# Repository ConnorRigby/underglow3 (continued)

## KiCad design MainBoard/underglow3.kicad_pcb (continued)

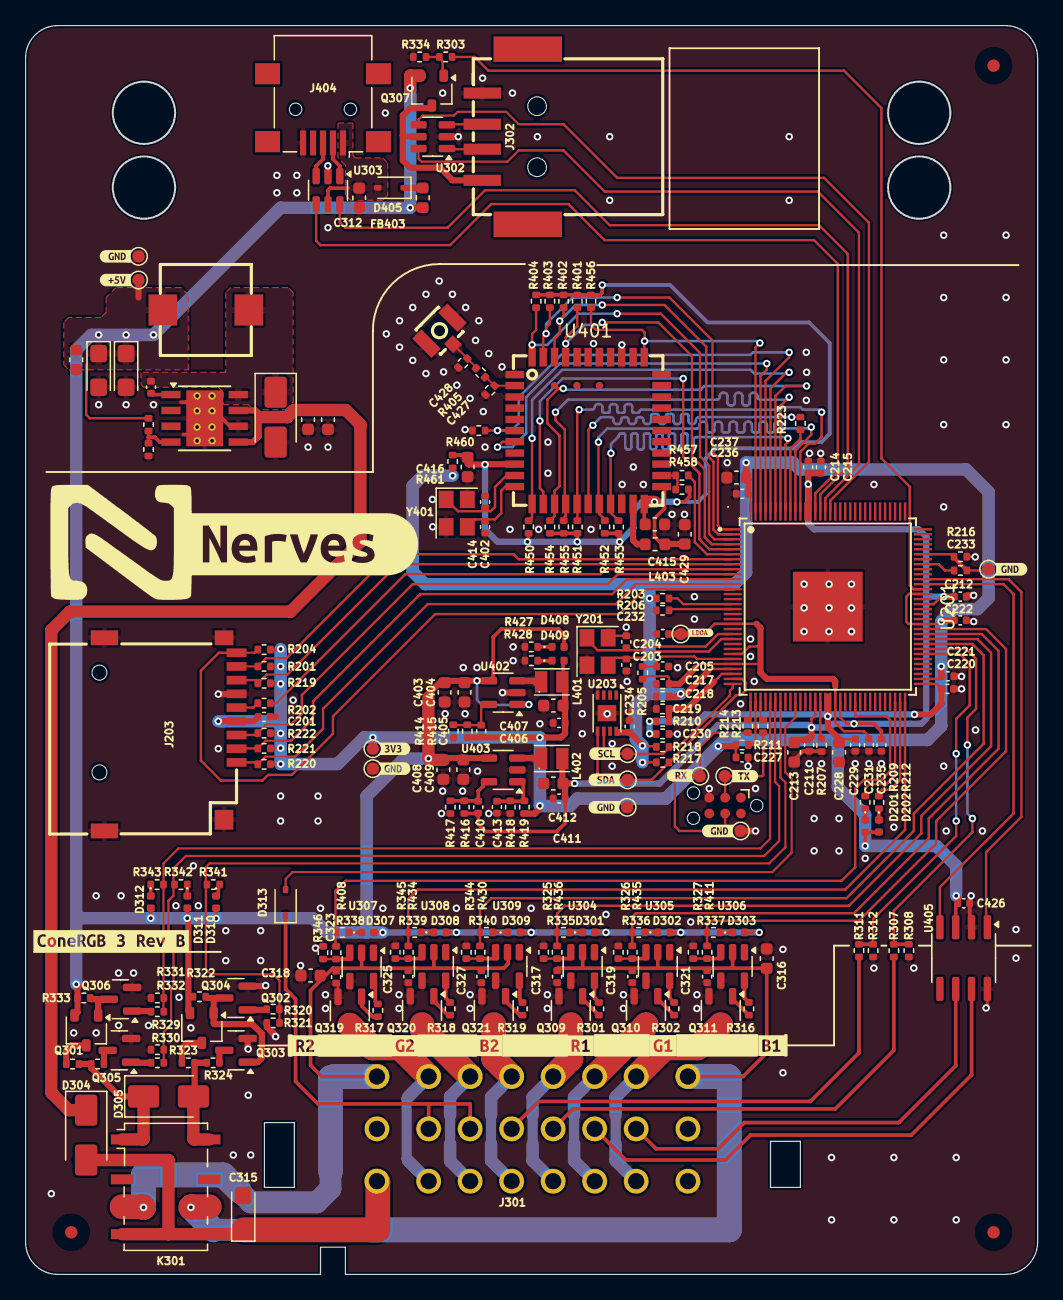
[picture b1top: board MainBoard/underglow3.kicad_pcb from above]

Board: 4 copper layers, 81.2 x 100.2 mm, 246 parts (0 on the bottom side), 145 nets.

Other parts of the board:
Enclosure: TestPoint_Pad_D1.0mm
TP: GND; TestPoint_Pad_D1.0mm
TP#2: GND; TestPoint_Pad_D1.0mm
U201: T113-S3; LQFP-128_L14.0-W14.0-P0.40-LS16.0-BL-EP5.6
kibuzzard-65F09AC9: G***; kibuzzard-65F09AC9
kibuzzard-65F09B04: G***; kibuzzard-65F09B04
kibuzzard-65F09B16: G***; kibuzzard-65F09B16
kibuzzard-65F09B27: G***; kibuzzard-65F09B27
kibuzzard-65F09B40: G***; kibuzzard-65F09B40
kibuzzard-65F09B51: G***; kibuzzard-65F09B51
kibuzzard-65F09C6B: G***; kibuzzard-65F09C6B
kibuzzard-65F09CD2: G***; kibuzzard-65F09CD2
kibuzzard-65F09CF9: G***; kibuzzard-65F09CF9
kibuzzard-65F09D0C: G***; kibuzzard-65F09D0C
kibuzzard-65F09D1C, kibuzzard-65F09D1C#2: G***; kibuzzard-65F09D1C
kibuzzard-65FE52BD: G***; kibuzzard-65FE52BD
kibuzzard-65FE522B: G***; kibuzzard-65FE522B
kibuzzard-65FEF020: G***; kibuzzard-65FEF020
kibuzzard-65FEF408: G***; kibuzzard-65FEF408
kibuzzard-65FEF568: G***; kibuzzard-65FEF568
kibuzzard-666C6B51: G***; kibuzzard-666C6B51
kibuzzard-6669C582: G***; kibuzzard-6669C582
kibuzzard-6669C587: G***; kibuzzard-6669C587

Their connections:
+0v9: U201.46 (VDD-SYS0), U201.51 (VDD-SYS0), U201.81 (VDD-SYS2), U201.116 (VDD-CORE0), U201.117 (VDD-CORE1); also elsewhere on the board
+1V8A: U201.89 (AVCC); also elsewhere on the board
+3V3: U201.29 (LDO-IN), U201.66 (VCC-PD), U201.77 (VCC-TVOUT), U201.83 (VCC-IO), U201.128 (VCC-PG); also elsewhere on the board
/Application/AP_WAKE_BT: U201.125 (PG13); also elsewhere on the board
/Application/BT_EN: U201.127 (PG15); also elsewhere on the board
/Application/BT_WAKE_AP: U201.126 (PG14); also elsewhere on the board
/Application/CAN0_RX: U201.85 (PB3); also elsewhere on the board
/Application/CAN0_TX: U201.86 (PB2); also elsewhere on the board
/Application/DZQ: U201.47 (DZQ); also elsewhere on the board
/Application/HCI_CTS: U201.4 (PG9); also elsewhere on the board
/Application/HCI_RTS: U201.3 (PG8); also elsewhere on the board
/Application/HCI_RX: U201.2 (PG7); also elsewhere on the board
/Application/HCI_TX: U201.1 (PG6); also elsewhere on the board
/Application/I2C_SCL: U201.32 (PE12); also elsewhere on the board
/Application/I2C_SDA: U201.31 (PE13); also elsewhere on the board
/Application/LDOA_OUT: U201.20 (VCC-PLL), U201.26 (VCC-RTC), U201.28 (LDOA-OUT), U201.50 (VDD18-DRAM); also elsewhere on the board
/Application/LDOB_OUT: U201.30 (LDOB-OUT); also elsewhere on the board
/Application/LEDC: U201.42 (PE5); also elsewhere on the board
/Application/LED_ST1: U201.62 (PD7); also elsewhere on the board
/Application/LED_ST2: U201.63 (PD8); also elsewhere on the board
/Application/PWM0: U201.73 (PD16); also elsewhere on the board
/Application/PWM1: U201.74 (PD17); also elsewhere on the board
/Application/PWM2: U201.75 (PD18); also elsewhere on the board
/Application/PWM3: U201.76 (PD19); also elsewhere on the board
/Application/PWM4: U201.54 (PD20); also elsewhere on the board
/Application/PWM6: U201.64 (PD9); also elsewhere on the board
/Application/RELAY_COIL_GND: U201.38 (PE9); also elsewhere on the board
/Application/RELAY_COIL_VDC: U201.37 (PE10); also elsewhere on the board
/Application/RELAY_SW: U201.39 (PE8); also elsewhere on the board
/Application/RST: U201.27 (RST); also elsewhere on the board
/Application/SDCO0_CLK: U201.9 (PF2); also elsewhere on the board
/Application/SDCO0_CMD: U201.10 (PF3); also elsewhere on the board
/Application/SDCO0_D0: U201.8 (PF1); also elsewhere on the board
/Application/SDCO0_D1: U201.7 (PF0); also elsewhere on the board
/Application/SDCO0_D2: U201.12 (PF5); also elsewhere on the board
/Application/SDCO0_D3: U201.11 (PF4); also elsewhere on the board
/Application/SD_DET: U201.13 (PF6); also elsewhere on the board
/Application/SPI0_CLK: U201.19 (PC2); also elsewhere on the board
/Application/SPI0_CS0: U201.18 (PC3); also elsewhere on the board
/Application/SPI0_HLD: U201.14 (PC7); also elsewhere on the board
/Application/SPI0_MISO: U201.16 (PC5); also elsewhere on the board
/Application/SPI0_MOSI: U201.17 (PC4); also elsewhere on the board
/Application/SPI0_WP: U201.15 (PC6); also elsewhere on the board
/Application/SUS_CLK: U201.6 (PG11); also elsewhere on the board
/Application/UART0_RX: U201.33 (PE3); also elsewhere on the board
/Application/UART0_TX: U201.35 (PE2); also elsewhere on the board
/Application/USB_SW: U201.84 (PB4); also elsewhere on the board
/Application/VCC_DRAM: U201.48 (VCC-DRAM0), U201.49 (VCC-DRAM1), U201.65 (VCC-LVDS); also elsewhere on the board
/Application/VCC_PE: U201.34 (VCC-PE); also elsewhere on the board
/Application/WIFI_CMD: U201.118 (PG1); also elsewhere on the board
/Application/WIFI_DAT0: U201.119 (PG2); also elsewhere on the board
/Application/WIFI_DAT1: U201.121 (PG3); also elsewhere on the board
/Application/WIFI_DAT2: U201.123 (PG4); also elsewhere on the board
/Application/WIFI_DAT3: U201.122 (PG5); also elsewhere on the board
/Application/WL_REG_ON: U201.124 (PG12); also elsewhere on the board
/Application/WL_WAKE_AP: U201.5 (PG10); also elsewhere on the board
/Application/XI: U201.23 (DXIN); also elsewhere on the board
/Application/XO: U201.22 (DXOUT); also elsewhere on the board
/Power/PI1_DIV: U201.72 (PD15); also elsewhere on the board
/Power/PI2_DIV: U201.71 (PD14); also elsewhere on the board
/Power/USB0_DN: U201.114 (USB0-DM); also elsewhere on the board
/Power/USB0_DP: U201.115 (USB0-DP); also elsewhere on the board
/Power/USB1_DN: U201.113 (USB1-DM); also elsewhere on the board
/Power/USB1_DP: U201.112 (USB1-DP); also elsewhere on the board
GND: TP.1, TP#2.1, U201.129 (EP); also elsewhere on the board
GNDA: U201.91 (AGND); also elsewhere on the board
unnamed 130: U201.120 (PG0); also elsewhere on the board

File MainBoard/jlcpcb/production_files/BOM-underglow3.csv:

Comment,Designator,Footprint,LCSC
450mΩ ±25% 600Ω@100MHz,FB403,L_0603_1608Metric,C1002
1k,"R209,R212,R301,R302,R303,R316,R317,R318,R319,R320,R330,R332,R335,R336,R337,R338,R339,R340,R341,R342,R343,R408,R411,R427,R428,R430,R434,R435,R436",R_0402_1005Metric,C11702
SN65HVD230,U405,SOIC-8_3.9x4.9mm_P1.27mm,C12084
2.2uF,"C217,C218,C219,C233",R_0402_1005Metric,C12530
SS210,"D304,D305,D306",D_SMA,C14996
22pF,"C203,C204,C405,C410",C_0402_1005Metric,C1555
0R,"R210,R211,R213,R214,R216,R405,R457,R460,R461",R_0402_1005Metric,C17168
NSR0320MW2T1G,"D313,D405",D_SOD-323,C191023
10uF,"C316,C318,C403,C404,C407,C408,C409,C412",C_0603_1608Metric,C19702
SI2302-TP,"Q309,Q310,Q311,Q319,Q320,Q321",SOT-23-3,C20917
24Mhz,Y201,Crystal_SMD_3225-4Pin_3.2x2.5mm,C2149059
G6K-2F-Y-TR DC3,K301,Relay_DPDT_Omron_G6K-2F-Y,C2153097
22R,"R202,R223,R306,R323,R324,R328",R_0402_1005Metric,C25092
240R,R207,R_0402_1005Metric,C25094
100k,"R201,R203,R204,R205,R206,R219,R220,R221,R222,R321,R322,R325,R326,R327,R329,R331,R333,R334,R344,R345,R346,R419,R450,R456",R_0402_1005Metric,C25741
10k,"R307,R311,R347",R_0402_1005Metric,C25744
150k,"R415,R417,R418",R_0402_1005Metric,C25755
47k,"R451,R452,R453,R454,R455,R458",R_0402_1005Metric,C25792
75k,R416,R_0402_1005Metric,C25798
2.2k,"R217,R218",R_0402_1005Metric,C25879
3.3k,R348,R_0402_1005Metric,C25890
4.7uH,L303,IND-SMD_L7.3-W7.3,C2826710
100nf,"C201,C205,C211,C212,C214,C215,C220,C221,C222,C227,C229,C231,C232,C234,C235,C236,C304,C317,C319,C321,C323,C325,C327,C406,C411,C413,C426",C_0402_1005Metric,C307331
LED,"D201,D202,D301,D302,D303,D307,D308,D309,D310,D311,D312,D408,D409",LED_0402_1005Metric,C364556
Micro_SD_Card_Det1,J203,TF-SMD_TF-PUSH,C393941
680k,R414,R_0402_1005Metric,C4131
SY8088IAAC,"U402,U403",SOT-23-5,C479072
BWU.FL-IPEX1,ANT401,IPEX-SMD_BWIPX-1-001E,C5137195
3.9k,"R308,R312",R_0402_1005Metric,C51721
T113-S3,U201,LQFP-128_L14.0-W14.0-P0.40-LS16.0-BL-EP5.6,C5197687
1uF,C230,R_0402_1005Metric,C52923
ATECC608A-MAHDA,U203,DFN-8-1EP_3x2mm_P0.5mm_EP1.3x1.5mm,C616908
10uF 16V,"C313,C314,C315",CP_EIA-3216-18_Kemet-A,C7171
USB_A,J302,USB-A-SMD_USB-234-BCW,C720528
USB_B_Mini,J404,USB_Mini-B_Lumberg_2486_01_Horizontal,C720611
SRV05-4,"U302,U303",SOT-23-6,C7420376
SI2302-TP,"Q302,Q303,Q305,Q306",SOT-23,C77977
MCP1416T-E/OT,"U304,U305,U306,U307,U308,U309",SOT-23-5,C83775
AO3419,"Q301,Q304,Q307",SOT-23W,C88053
10uF,"C213,C228,C237,C302,C303,C311,C312,C415,C416",C_0603_1608Metric,C96446
2.2uH,"L401,L402",IND-SMD_L2.0-W1.6_VLS201610CX-150M,C97005
TPS5430DDA,U310,TI_SO-PowerPAD-8_ThermalVias,C9864
RL-SM02BD-8723BS,U401,QFN-44_L12.0-W12.0-P0.90-TL_AP6212,C9900101851

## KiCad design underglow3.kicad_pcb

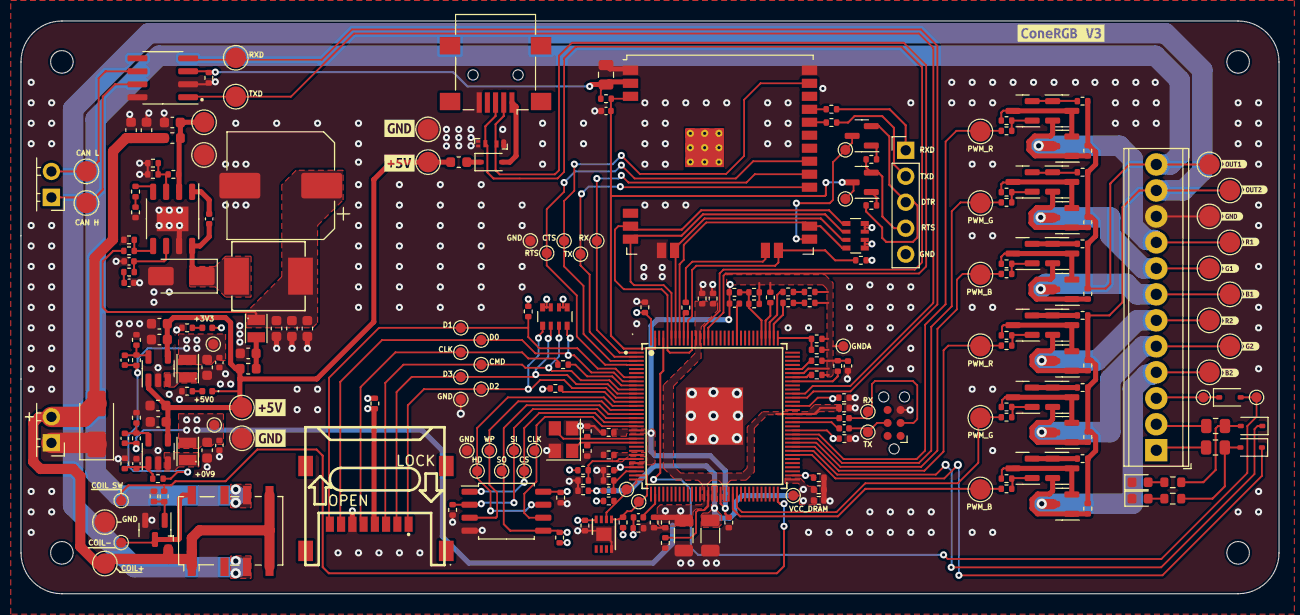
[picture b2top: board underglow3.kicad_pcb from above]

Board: 4 copper layers, 123.0 x 56.0 mm, 270 parts (0 on the bottom side), 143 nets.

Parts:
C201, C202, C205, C206, C209, C210, C211, C212, C214, C215, C216, C220, C221, C222, C223, C226, C227, C229, C231, C232, C234, C235, C236, C426: 100nf; R_0402_1005Metric
C203, C204: 22pF; R_0402_1005Metric
C207, C208: 470nF; R_0402_1005Metric
C213, C228: 10uF; C_1206_3216Metric
C217, C218, C219, C224, C233: 2.2uF; R_0402_1005Metric
C225: 1nF; R_0402_1005Metric
C230, C416: 1uF; R_0402_1005Metric
C301, C402, C406, C411, C413: 100nF; C_0402_1005Metric
C302: 1uF; C_0805_2012Metric
C403, C404, C407, C408, C409, C412, C421, C422, C425: 10uF; C_0603_1608Metric
C405, C410, C418: 22pF; C_0402_1005Metric
C414, C415: 47uF; C_0603_1608Metric
C419: 3.3nF; C_0402_1005Metric
C420: 220uF 16V; CP_Elec_10x10
C423: 220nF; C_0603_1608Metric
C424: 68pF; C_0603_1608Metric
D401, D403, D404: AU0511P1; Diodes_DFN1006-3
D402, D412: 1N5819WS; D_SOD-323
D405, D410: NSR0320MW2T1G; D_SOD-323
D406: SMAJ12CA; D_SMA
D407: SS54; D_SMA
D408, D409: LED; LED_0402_1005Metric
D411, D413: LED_0603_RED; LED_0603_1608Metric
FB401, FB402, FB403: 220R@100MHz; L_0603_1608Metric
H401, H402, H403, H404: MountingHole; MountingHole_2.2mm_M2
J201: XKTF-1307-16; TF-SMD_YC39-TF08-180
J202: TC2030-IDC; Tag-Connect_TC2030-IDC-NL_2x03_P1.27mm_Vertical
J301: ESP32; PinHeader_1x05_P2.54mm_Vertical
J401, J402: Conn_01x02; PinHeader_1x02_P2.54mm_Horizontal
J403: Conn_01x12; TerminalBlock_Phoenix_MPT-0,5-12-2.54_1x12_P2.54mm_Horizont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
J404: USB_B_Mini; USB_Mini-B_Lumberg_2486_01_Horizontal
K401: G6K-2; Relay_DPDT_Omron_G6K-2F-Y
L401, L402, L404: 2.2uH; IND-SMD_L2.0-W1.6_VLS201610CX-150M
L403: 8.2uH 3.7A; IND-SMD_L7.0-W6.6_FXL0630
Q301, Q302, Q401, Q402, Q403, Q405, Q406, Q408, Q409, Q411, Q412, Q413, Q414, Q415, Q416: BC850; SOT-23
Q404, Q407, Q410, Q417, Q418, Q419: SI2302-TP; SOT-23
R201, R203, R204, R205, R206, R212, R301, R304, R419: 100k; R_0402_1005Metric
R202, R302, R307, R308: 22R; R_0402_1005Metric
R207: 240R; R_0402_1005Metric
R208, R209: 27R; R_0402_1005Metric
R210, R211, R213, R214, R215, R216: 0R; C_0402_1005Metric
R217, R218: 1.8k; R_0402_1005Metric
R305, R306: 12k; R_0402_1005Metric
R401, R407, R412, R423, R425, R426, R431, R437, R438, R439: 100k 1%; R_0402_1005Metric
R402, R408, R409, R410, R411, R413, R427, R428, R429, R430, R432, R433, R434, R435, R436, R440, R441, R442, R443, R444, R445: 1k; R_0402_1005Metric
R403, R405: 10k; R_0805_2012Metric
R404, R406: 2.2k; R_0603_1608Metric
R414: 680k; R_0402_1005Metric
R415, R417, R418: 150k; R_0402_1005Metric
R416: 75k; R_0402_1005Metric
R420, R421: 0R; R_0402_1005Metric
R422: 33k 1%; R_0402_1005Metric
R424: 18.7k 1%; R_0402_1005Metric
RN201, RN301: 100k; R_Array_Convex_4x0603
TP201: DAT2; TestPoint_Pad_D1.0mm
TP202: DAT3; TestPoint_Pad_D1.0mm
TP203: CMD; TestPoint_Pad_D1.0mm
TP204, TP208: CLK; TestPoint_Pad_D1.0mm
TP205: DAT0; TestPoint_Pad_D1.0mm
TP206: DAT1; TestPoint_Pad_D1.0mm
TP207: CS0; TestPoint_Pad_D1.0mm
TP209: MISO; TestPoint_Pad_D1.0mm
TP210: MOSI; TestPoint_Pad_D1.0mm
TP211: WP; TestPoint_Pad_D1.0mm
TP212: HLD; TestPoint_Pad_D1.0mm
TP213: SDA; TestPoint_Pad_D1.0mm
TP214: SCL; TestPoint_Pad_D1.0mm
TP215: RXD; TestPoint_Pad_D1.0mm
TP216: TXD; TestPoint_Pad_D1.0mm
TP217: SD_GND; TestPoint_Pad_D1.0mm
TP218: FLASH_GND; TestPoint_Pad_D1.0mm
TP219: AGND; TestPoint_Pad_D1.0mm
TP220: VCC_DRAM; TestPoint_Pad_D1.0mm
TP301: EN; TestPoint_Pad_D1.0mm
TP302: IO0; TestPoint_Pad_D1.0mm
TP303: RX; TestPoint_Pad_D1.0mm
TP304: TX; TestPoint_Pad_D1.0mm
TP305: CTS; TestPoint_Pad_D1.0mm
TP306: RTS; TestPoint_Pad_D1.0mm
TP307: HCI_GND; TestPoint_Pad_D1.0mm
TP401: CAN_TX; TestPoint_Pad_D2.0mm
TP402: CAN_RX; TestPoint_Pad_D2.0mm
TP403: CAN_H; TestPoint_Pad_D2.0mm
TP404: CAN_L; TestPoint_Pad_D2.0mm
TP405: USB_5V; TestPoint_Pad_D2.0mm
TP406: PWM_R1; TestPoint_Pad_D2.0mm
TP407: PWM_G1; TestPoint_Pad_D2.0mm
TP408: PWM_B1; TestPoint_Pad_D2.0mm
TP409: PWM_G2; TestPoint_Pad_D2.0mm
TP410: PWM_B2; TestPoint_Pad_D2.0mm
TP411: PWM_R2; TestPoint_Pad_D2.0mm
TP412: RGB_R1; TestPoint_Pad_D2.0mm
TP413: RGB_G1; TestPoint_Pad_D2.0mm
TP414: RGB_B1; TestPoint_Pad_D2.0mm
TP415: RGB_R2; TestPoint_Pad_D2.0mm
TP416: RGB_G2; TestPoint_Pad_D2.0mm
TP417: RGB_B2; TestPoint_Pad_D2.0mm
TP418: USB_GND; TestPoint_Pad_D2.0mm
TP419: +12V; TestPoint_Pad_D2.0mm
TP420: +12V_gnd; TestPoint_Pad_D2.0mm
TP421: RGB2; TestPoint_Pad_D2.0mm
TP422: RGB1; TestPoint_Pad_D2.0mm
TP423: +3v3; TestPoint_Pad_D1.0mm
TP424: LEDC; TestPoint_Pad_D1.0mm
TP425: LEDC_OUT; TestPoint_Pad_D1.0mm
TP426: RELAY_VIN; TestPoint_Pad_D2.0mm
TP427: RELAY_GND; TestPoint_Pad_D2.0mm
TP428: RELAY_SW; TestPoint_Pad_D1.0mm
TP429: RELAY_COIL-; TestPoint_Pad_D1.0mm
TP430: +5V_IN_3V3; TestPoint_Pad_D2.0mm
TP431: +5V_IN_3V3_GND; TestPoint_Pad_D2.0mm
TP432: RGB_GND; TestPoint_Pad_D2.0mm
TP433: +0V9; TestPoint_Pad_D1.0mm
U201: T113-S3; LQFP-128_L14.0-W14.0-P0.40-LS16.0-BL-EP5.6
U202: W25Q32JVSS; SOIC-8_5.23x5.23mm_P1.27mm
U203: ATECC608A-MAHDA; DFN-8-1EP_3x2mm_P0.5mm_EP1.3x1.5mm
U301: ESP32-WROOM-32U
U402, U403: SY8088IAAC; SOT-23-5
U404: SCT2650STER; HSOP-8-1EP_3.9x4.9mm_P1.27mm_EP2.41x3.1mm
U405: SN65HVD230; SOIC-8_3.9x4.9mm_P1.27mm
Y201: 24Mhz; Crystal_SMD_3225-4Pin_3.2x2.5mm
kibuzzard-65CD0D8E, kibuzzard-65CD0D8E#2: G***; kibuzzard-65CD0D8E
kibuzzard-65CD0DAC, kibuzzard-65CD0DAC#2: G***; kibuzzard-65CD0DAC
kibuzzard-65CD11A4: G***; kibuzzard-65CD11A4
kibuzzard-65CD11AE: G***; kibuzzard-65CD11AE
kibuzzard-65CD11B5: G***; kibuzzard-65CD11B5
kibuzzard-65CD11BE: G***; kibuzzard-65CD11BE
kibuzzard-65CD116A: G***; kibuzzard-65CD116A
kibuzzard-65CD117C: G***; kibuzzard-65CD117C
kibuzzard-65CD119A: G***; kibuzzard-65CD119A
kibuzzard-65CD1184: G***; kibuzzard-65CD1184
kibuzzard-65CD1191: G***; kibuzzard-65CD1191
kibuzzard-65CD1209: G***; kibuzzard-65CD1209

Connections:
+0v9: C211.1, C212.1, C213.1, C214.1, C215.1, C235.1, C410.1, C411.1, C412.1, L402.2, R416.1, TP433.1, U201.46 (VDD-SYS0), U201.51 (VDD-SYS0), U201.81 (VDD-SYS2), U201.116 (VDD-CORE0), U201.117 (VDD-CORE1)
+1V8A: C233.1, U201.89 (AVCC)
+3V3: C201.1, C202.1, C216.2, C218.1, C221.1, C222.1, C227.1, C234.1, C236.1, C302.1, C405.1, C406.1, C407.1, C426.1, D409.1 (K), J201.4, L401.2, R201.1, R203.1, R204.1, R205.1, R211.2, R217.1, R218.1, R301.1, R304.1, R414.1, R419.1, RN201.5 (R4.2), RN201.6 (R3.2), RN201.7 (R2.2), RN201.8 (R1.2), RN301.5 (R4.2), RN301.6 (R3.2), RN301.7 (R2.2), RN301.8 (R1.2), TP423.1, U201.29 (LDO-IN), U201.66 (VCC-PD), U201.77 (VCC-TVOUT), U201.83 (VCC-IO), U201.128 (VCC-PG), U202.8 (VCC), U203.8 (VCC), U301.2 (VDD), U405.3 (VCC)
+5V: C403.1, C404.1, C408.1, C409.1, D408.1 (K), FB402.2, FB403.2, TP405.1, TP430.1, U402.1 (EN), U402.4 (IN), U403.4 (IN)
+12V: C425.1, FB401.2, R421.1, TP419.1, U404.2 (VIN)
/Application/CAN0_RX: TP402.1, U201.85 (PB3), U405.4 (R)
/Application/CAN0_TX: TP401.1, U201.86 (PB2), U405.1 (D)
/Application/DI1: D402.1 (K), U201.72 (PD15)
/Application/DI2: D412.1 (K), U201.71 (PD14)
/Application/DZQ: R207.1, U201.47 (DZQ)
/Application/GPADC0: C225.1, C226.1, R212.2, U201.101 (GPADC0)
/Application/HPOUFB: C206.1, U201.100 (HPOUTFB)
/Application/HPOUTL: C209.1, U201.99 (HPOUTL)
/Application/HPOUTR: C210.1, U201.98 (HPOUTR)
/Application/HPVCC: C223.1, C224.1, U201.97 (HPVCC)
/Application/I2C_SCL: R218.2, TP214.1, U201.32 (PE12), U203.6 (SCL)
/Application/I2C_SDA: R217.2, TP213.1, U201.31 (PE13), U203.5 (SDA)
/Application/LDOA_OUT: C217.1, C231.1, C232.1, R212.1, R215.1, U201.20 (VCC-PLL), U201.26 (VCC-RTC), U201.28 (LDOA-OUT), U201.50 (VDD18-DRAM)
/Application/LDOB_OUT: C219.1, R210.1, U201.30 (LDOB-OUT)
/Application/LEDC: D410.2 (A), TP424.1, U201.125 (PG13)
/Application/PWM0: R434.2, TP411.1, U201.73 (PD16)
/Application/PWM1: R430.2, TP408.1, U201.74 (PD17)
/Application/PWM2: R411.2, TP407.1, U201.75 (PD18)
/Application/PWM3: R408.2, TP406.1, U201.76 (PD19)
/Application/PWM4: R435.2, TP409.1, U201.54 (PD20)
/Application/PWM5: R436.2, TP410.1, U201.53 (PD21)
/Application/PWM6: R402.2, TP428.1, U201.64 (PD9)
/Application/RST: C205.1, R205.2, U201.27 (RST)
/Application/RXD: J202.3, R213.2, TP215.1
/Application/SDCO0_CLK: R202.2, U201.9 (PF2)
/Application/SDCO0_CMD: J201.3, RN201.3 (R3.1), TP203.1, U201.10 (PF3)
/Application/SDCO0_D0: J201.7, RN201.4 (R4.1), TP205.1, U201.8 (PF1)
/Application/SDCO0_D1: J201.8, R201.2, TP206.1, U201.7 (PF0)
/Application/SDCO0_D2: J201.1, RN201.1 (R1.1), TP201.1, U201.12 (PF5)
/Application/SDCO0_D3: J201.2, RN201.2 (R2.1), TP202.1, U201.11 (PF4)
/Application/SD_CLK: J201.5, R202.1, TP204.1
/Application/SD_DET: R204.2, U201.13 (PF6)
/Application/SPI0_CLK: TP208.1, U201.19 (PC2), U202.6 (CLK)
/Application/SPI0_CS0: TP207.1, U201.18 (PC3), U202.1 (~CS)
/Application/SPI0_HLD: TP212.1, U201.14 (PC7), U202.7 (IO3)
/Application/SPI0_MISO: R203.2, TP209.1, U201.16 (PC5), U202.5 (DI(IO0))
/Application/SPI0_MOSI: R206.1, TP210.1, U201.17 (PC4), U202.2 (DO(IO1))
/Application/SPI0_WP: TP211.1, U201.15 (PC6), U202.3 (IO2)
/Application/TXD: J202.4, R214.1, TP216.1
/Application/UART3_RX: R214.2, U201.79 (PB7)
/Application/UART3_TX: R213.1, U201.80 (PB6)
/Application/USB0_DM: D403.3 (K), J404.2 (D-), U201.114 (USB0-DM)
/Application/USB0_DP: D404.3 (K), J404.3 (D+), U201.115 (USB0-DP)
/Application/VCC_DRAM: C220.1, C228.1, C229.1, C230.1, R210.2, TP220.1, U201.48 (VCC-DRAM0), U201.49 (VCC-DRAM1), U201.65 (VCC-LVDS)
/Application/VCC_PE: R211.1, U201.34 (VCC-PE)
/Application/VCC_TVIN: R215.2, U201.107 (VCC-TVIN)
/Application/VRA1: C208.1, U201.92 (VRA1)
/Application/VRA2: C207.1, U201.90 (VRA2)
/Application/WIFI_CLK: R302.2, U201.120 (PG0)
/Application/XI: C203.1, U201.23 (DXIN), Y201.1
/Application/XO: C204.1, U201.22 (DXOUT), Y201.3
/Power/CAN_H: J402.1, TP403.1, U405.7 (CANH)
/Power/CAN_L: J402.2, TP404.1, U405.6 (CANL)
/Power/COMP: C418.1, R422.1, U404.6 (COMP)
/Power/FB: R423.2, R424.1, U404.5 (FB)
/Power/LEDC_OUT: D410.1 (K), J403.3, TP425.1
/Power/PI1: J403.2, R403.1
/Power/PI1_DIV: D402.2 (A), R403.2, R404.1
/Power/PI2: J403.1, R405.1
/Power/PI2_DIV: D412.2 (A), R405.2, R406.1
/Power/RGB1_OUT: J403.12, K401.6, R409.1, R410.1, R413.1, R429.1, R432.1, R433.1, TP422.1
/Power/RGB2_OUT: J403.11, K401.3, R440.1, R441.1, R442.1, R443.1, R444.1, R445.1, TP421.1
/Power/RGB_B1: J403.7, Q410.3 (D), TP414.1
/Power/RGB_B2: J403.4, Q419.3 (D), TP417.1
/Power/RGB_G1: J403.8, Q407.3 (D), TP413.1
/Power/RGB_G2: J403.5, Q418.3 (D), TP416.1
/Power/RGB_R1: J403.9, Q404.3 (D), TP412.1
/Power/RGB_R2: J403.6, Q417.3 (D), TP415.1
/Power/SW: C402.2, D407.1 (K), L403.1, U404.8 (SW)
/Power/VBUS: D405.2 (A), J404.1 (VBUS)
/Power/VBUS_FB: D405.1 (K), FB403.1
/Power/VIN: C414.1, C415.1, D401.3 (K), D406.2 (A2), FB401.1, J401.2, K401.1, K401.4, K401.5, TP426.1
/WiFi+BT/BOOT_DTR: J301.3, Q302.2 (E), R305.1
/WiFi+BT/BOOT_RTS: J301.4, Q301.2 (E), R306.1
/WiFi+BT/BOOT_RXD: J301.1, R307.2
/WiFi+BT/BOOT_TXD: J301.2, R308.2
/WiFi+BT/EN: C301.1, Q301.3 (C), R304.2, TP301.1, U201.127 (PG15), U301.3 (EN)
/WiFi+BT/HCI_CTS: TP306.1, U201.3 (PG8), U301.37 (IO23)
/WiFi+BT/HCI_RTS: TP305.1, U201.4 (PG9), U301.31 (IO19)
/WiFi+BT/HCI_RX: TP304.1, U201.1 (PG6), U301.30 (IO18)
/WiFi+BT/HCI_TX: TP303.1, U201.2 (PG7), U301.29 (IO5)
/WiFi+BT/IO0: Q302.3 (C), TP302.1, U301.25 (IO0)
/WiFi+BT/RXD0: R307.1, U301.35 (TXD0/IO1)
/WiFi+BT/SDIO_CLK: R302.1, U301.23 (IO15)
/WiFi+BT/SDIO_CMD: RN301.1 (R1.1), U201.118 (PG1), U301.13 (IO14)
/WiFi+BT/SDIO_DAT0: R301.2, U201.119 (PG2), U301.24 (IO2)
/WiFi+BT/SDIO_DAT1: RN301.4 (R4.1), U201.121 (PG3), U301.26 (IO4)
/WiFi+BT/SDIO_DAT2: RN301.2 (R2.1), U201.123 (PG4), U301.14 (IO12)
/WiFi+BT/SDIO_DAT3: RN301.3 (R3.1), U201.122 (PG5), U301.16 (IO13)
/WiFi+BT/TXD0: R308.1, U301.34 (RXD0/IO3)
GND: C201.2, C202.2, C203.2, C204.2, C205.2, C211.2, C212.2, C213.2, C214.2, C215.2, C216.1, C217.2, C218.2, C219.2, C220.2, C221.2, C222.2, C227.2, C228.2, C229.2, C230.2, C231.2, C232.2, C234.2, C235.2, C236.2, C301.2, C302.2, C403.2, C404.2, C406.2, C407.2, C408.2, C409.2, C411.2, C412.2, C413.2, C414.2, C415.2, C416.2, C418.2, C419.2, C420.2, C421.2, C422.2, C423.2, C424.2, C425.2, C426.2, D403.1 (A1), D403.2 (A2), D404.1 (A1), D404.2 (A2), D406.1 (A1), D407.2 (A), D411.1 (K), D413.1 (K), J201.6, J202.5, J301.5, J401.1, J403.10, J404.5 (GND), Q401.2 (E), R206.2, R207.2, R216.1, R401.2, R415.2, R417.2, R418.1, R420.2, R424.2, R426.2, R427.1, R428.1, TP217.1, TP218.1, TP307.1, TP418.1, TP420.1, TP427.1, TP431.1, TP432.1, U201.129 (EP), U202.4 (GND), U203.4 (GND), U203.9 (EP), U301.1 (GND), U301.15 (GND), U301.38 (GND), U301.39 (GND), U402.2 (GND), U403.2 (GND), U404.7 (GND), U404.9 (EP), U405.2 (GND), U405.8 (Rs), Y201.2, Y201.4
GNDA: C206.2, C207.2, C208.2, C223.2, C224.2, C225.2, C226.2, C233.2, R208.2, R209.2, R216.2, TP219.1, U201.91 (AGND)
unnamed: C209.2, R209.1
unnamed: C210.2, R208.1
unnamed: C419.1, R422.2
unnamed: C420.1, C421.1, C423.1, C424.1, L403.2, L404.1, R423.1
unnamed: C422.1, FB402.1, L404.2
unnamed: D401.1 (A1), D401.2 (A2), K401.8, Q401.3 (C), TP429.1
unnamed: D408.2 (A), R427.2
unnamed: D409.2 (A), R428.2
unnamed: D411.2 (A), R404.2
unnamed: D413.2 (A), R406.2
unnamed: Q301.1 (B), R305.2
unnamed: Q302.1 (B), R306.2
unnamed: Q401.1 (B), R401.1, R402.1
unnamed: Q402.1 (B), R407.1, R408.1
unnamed: Q402.3 (C), Q403.3 (C), Q404.2 (S), R407.2
unnamed: Q402.2 (E), Q403.1 (B), R409.2
unnamed: Q403.2 (E), Q404.1 (G), R410.2
unnamed: Q405.1 (B), R411.1, R412.1
unnamed: Q405.3 (C), Q406.3 (C), Q407.2 (S), R412.2
unnamed: Q405.2 (E), Q406.1 (B), R413.2
unnamed: Q406.2 (E), Q407.1 (G), R429.2
unnamed: Q408.1 (B), R430.1, R431.1
unnamed: Q408.3 (C), Q409.3 (C), Q410.2 (S), R431.2
unnamed: Q408.2 (E), Q409.1 (B), R432.2
unnamed: Q409.2 (E), Q410.1 (G), R433.2
unnamed: Q411.1 (B), R434.1, R437.1
unnamed: Q411.3 (C), Q414.3 (C), Q417.2 (S), R437.2
unnamed: Q411.2 (E), Q414.1 (B), R440.2
unnamed: Q412.1 (B), R435.1, R438.1
unnamed: Q412.3 (C), Q415.3 (C), Q418.2 (S), R438.2
unnamed: Q412.2 (E), Q415.1 (B), R441.2
unnamed: Q413.1 (B), R436.1, R439.1
unnamed: Q413.3 (C), Q416.3 (C), Q419.2 (S), R439.2
unnamed: Q413.2 (E), Q416.1 (B), R442.2
unnamed: Q414.2 (E), Q417.1 (G), R443.2
unnamed: Q415.2 (E), Q418.1 (G), R444.2
unnamed: Q416.2 (E), Q419.1 (G), R445.2
unnamed: R425.2, R426.1
unnamed: C405.2, R414.2, R415.1, U402.5 (FB)
unnamed: L401.1, U402.3 (LX)
unnamed: C413.1, R418.2, R419.2, U403.1 (EN)
unnamed: C410.2, R416.2, R417.1, U403.5 (FB)
unnamed: L402.1, U403.3 (LX)
unnamed: C402.1, U404.1 (BOOT)
unnamed: C416.1, R420.1, R421.2, U404.3 (EN)
unnamed: R425.1, U404.4 (RT/CLK)

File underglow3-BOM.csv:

Item,Qty,Reference(s),Value,LibPart,Footprint,Datasheet,DNP,Color,Description,LCSC,MPN,Manual,Resistance,Sim.Device,Sim.Pins
1,24,"C201, C202, C205, C206, C209, C210, C211, C212, C214, C215, C216, C220, C221, C222, C223, C226, C227, C229, C231, C232, C234, C235, C236, C426",100nf,Device:C_Small,Capacitor_SMD:C_0402_1005Metric,~,,,,C307331,CL05B104KB54PNC,,,,
2,2,"C203, C204",22pF,Device:C_Small,Capacitor_SMD:C_0402_1005Metric,~,,,,C147430,C1005NP0220JGTS,,,,
3,2,"C207, C208",470nF,Device:C_Small,Resistor_SMD:R_0402_1005Metric,~,,,,C711580,GRT155R6YA474KE01D,,,,
4,2,"C213, C228",10uF,Device:C_Small,Capacitor_SMD:C_1206_3216Metric,~,,,,C13585,CL31A106KBHNNNE,,,,
5,5,"C217, C218, C219, C224, C233",2.2uF,Device:C_Small,Resistor_SMD:R_0402_1005Metric,~,,,,C12530,CL05A225MQ5NSNC,,,,
6,1,C225,1nF,Device:C_Small,Resistor_SMD:R_0402_1005Metric,~,,,,C106205,CC0402KRX7R9BB102,,,,
7,2,"C230, C416",1uF,Device:C_Small,Resistor_SMD:R_0402_1005Metric,~,,,,C52923,CL05A105KA5NQNC,,,,
8,5,"C301, C402, C406, C411, C413",100nF,Device:C,Capacitor_SMD:C_0402_1005Metric,~,,,,C307331,CL05B104KB54PNC,,,,
9,1,C302,1uF,Device:C,Capacitor_SMD:C_0805_2012Metric,~,,,,C28323,CL21B105KBFNNNE,,,,
10,9,"C403, C404, C407, C408, C409, C412, C421, C422, C425",10uF,Device:C,Capacitor_SMD:C_0603_1608Metric,~,,,,C466780,C0603X5R106M100NT,,,,
11,3,"C405, C410, C418",22pF,Device:C,Capacitor_SMD:C_0402_1005Metric,~,,,,C147430,C1005NP0220JGTS,,,,
12,2,"C414, C415",47uF,Device:C,Capacitor_SMD:C_0603_1608Metric,~,,,,C140782,GRM188R60J476ME15D,,,,
13,1,C419,3.3nF,Device:C,Capacitor_SMD:C_0402_1005Metric,~,,,,C107028,CC0402KRX7R9BB332,,,,
14,1,C420,220uF 16V,Device:C_Polarized,Capacitor_SMD:CP_Elec_10x10,https://datasheet.lcsc.com/lcsc/2304140030_Nichicon-UWT1H221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,,,,C125977,UWT1H221MNL1GS,,,,
15,1,C423,220nF,Device:C,Capacitor_SMD:C_0603_1608Metric,~,,,,C107083,CC0603KRX7R9BB224,,,,
16,1,C424,68pF,Device:C,Capacitor_SMD:C_0603_1608Metric,~,,,,C62782,CC0603JRNPO9BN680,,,,
17,3,"D401, D403, D404",AU0511P1,Device:D_TVS,Package_DFN_QFN:Diodes_DFN1006-3,~,,,,C19632468,AU0511P1,,,,
18,2,"D402, D412",1N5819WS,Diode:1N5819WS,Diode_SMD:D_SOD-323,https://datasheet.lcsc.com/lcsc/2204281430_Guangdong-Hottech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,,,,C191023,1N5819WS,,,,
19,2,"D405, D410",NSR0320MW2T1G,Device:D,Diode_SMD:D_SOD-323,~,,,,C48192,NSR0320MW2T1G,,,D,1=K 2=A
20,1,D406,SMAJ12CA,:D_TVS_1,Diode_SMD:D_SMA,https://datasheet.lcsc.com/lcsc/2304140030_GOODWORK-SMAJ12CA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,,,,C908818,SMAJ12CA,,,,
21,1,D407,SS54,Device:D,Diode_SMD:D_SMA,~,,,,C22452,SS54,,,D,1=K 2=A
22,2,"D408, D409",LED,Device:LED,LED_SMD:LED_0402_1005Metric,~,,,,C364556,LTST-C281KRKT,,,,
23,2,"D411, D413",LED_0603_RED,LCSC_LED:LED_0603_RED,LED_SMD:LED_0603_1608Metric,https://datasheet.lcsc.com/lcsc/1912111437_MEIHUA-MHT192CRCT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,,Red,,C389517,MHT192CRCT,,,,
24,3,"FB401, FB402, FB403",220R@100MHz,Device:FerriteBead,Inductor_SMD:L_0603_1608Metric,~,,,,C85827,BLM18EG221SN1D,,,,
25,1,J201,XKTF-1307-16,Connector_LCSC_SDCard:XKTF-1307-16,Connector_LCSC_SDCard:TF-SMD_YC39-TF08-180,https://item.szlcsc.com/318323.html,,,,C2885067,XKTF-1307-16,,,,
26,1,J403,Conn_01x12,Connector_Generic:Conn_01x12,"TerminalBlock_Phoenix:TerminalBlock_Phoenix_MPT-0,5-12-2.54_1x12_P2.54mm_Horizontal",~,,,,C918129,DB125-2.54-12P-GN-S,,,,
27,1,J404,USB_B_Mini,Connector:USB_B_Mini,Connector_USB:USB_Mini-B_Lumberg_2486_01_Horizontal,~,,,,C720611,UX-144S-ACP5,,,,
28,1,K401,G6K-2,Relay:G6K-2,Relay_SMD:Relay_DPDT_Omron_G6K-2F-Y,http://omronfs.omron.com/en_US/ecb/products/pdf/en-g6k.pdf,,,,C47190,G6K-2F-Y-TR DC5,,,,
29,3,"L401, L402, L404",2.2uH,Device:L,Inductor_LCSC:IND-SMD_L2.0-W1.6_VLS201610CX-150M,~,,,,C97005,WPN201610H2R2MT,,,,
30,1,L403,8.2uH 3.7A,Device:L,Inductor_LCSC:IND-SMD_L7.0-W6.6_FXL0630,~,,,,C18199424,YHNR4020-8R2M,,,,
31,15,"Q301, Q302, Q401, Q402, Q403, Q405, Q406, Q408, Q409, Q411, Q412, Q413, Q414, Q415, Q416",BC850,Transistor_BJT:BC850,Package_TO_SOT_SMD:SOT-23,http://www.infineon.com/dgdl/Infineon-BC847SERIES_BC848SERIE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,,,,C78484,BC850CLT1G,,,,
32,6,"Q404, Q407, Q410, Q417, Q418, Q419",SI2302-TP,Transistor_FET:BSS138,Package_TO_SOT_SMD:SOT-23,https://datasheet.lcsc.com/lcsc/1810010213_MCC-Micro-Commerc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,,," 20V 3A 1.25W 72mΩ@4.5V,3.6A 1.2V@50uA N Channel SOT-23 MOSFETs ROHS ",C77977,SI2302-TP,,,,
33,9,"R201, R203, R204, R205, R206, R212, R301, R304, R419",100k,Device:R,Resistor_SMD:R_0402_1005Metric,~,,,,C144732,AC0402JR-07100KL,,,,
34,4,"R202, R302, R307, R308",22R,Device:R,Resistor_SMD:R_0402_1005Metric,~,,,,C114765,RC0402FR-0722RL,,,,
35,1,R207,240R,Device:R,Resistor_SMD:R_0402_1005Metric,~,,,,C114755,RC0402FR-07240RL,,,,
36,2,"R208, R209",27R,Device:R_Small,Resistor_SMD:R_0402_1005Metric,~,,,,C138021,RC0402FR-0727RL,,,,
37,7,"R210, R211, R213, R214, R215, R216, R421",0R,Device:R_Small,Resistor_SMD:R_0402_1005Metric,~,,,,C17168,0402WGF0000TCE,,,,
38,2,"R217, R218",1.8k,Device:R,Resistor_SMD:R_0402_1005Metric,~,,,,C137909,RC0402JR-071K8L,,,,
39,2,"R305, R306",12k,Device:R,Resistor_SMD:R_0402_1005Metric,~,,,,C102781,RTT021202FTH,,,,
40,10,"R401, R407, R412, R423, R425, R426, R431, R437, R438, R439",100k 1%,Device:R,Resistor_SMD:R_0402_1005Metric,~,,,,C60491,RC0402FR-07100KL,,,,
41,19,"R402, R408, R409, R410, R411, R413, R429, R430, R432, R433, R434, R435, R436, R440, R441, R442, R443, R444, R445",1k,Device:R,Resistor_SMD:R_0402_1005Metric,~,,,,C11702,C11702,,,,
42,2,"R403, R405",10k,LCSC_Resistor:R_0805_10k,Resistor_SMD:R_0805_2012Metric,https://datasheet.lcsc.com/lcsc/2206010216_UNI-ROYAL-Uniroya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,,,,C17414,0805W8F1002T5E,,10kΩ,,
43,2,"R404, R406",2.2k,LCSC_Resistor:R_0603_DNP,Resistor_SMD:R_0603_1608Metric,https://datasheet.lcsc.com/lcsc/2206010130_UNI-ROYAL-Uniroya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,,,,C114762,RC0402FR-072K2L,,2.2k,,
44,1,R414,680k,Device:R,Resistor_SMD:R_0402_1005Metric,~,,,,C163456,RC0402FR-07680KL,,,,
45,3,"R415, R417, R418",150k,Device:R,Resistor_SMD:R_0402_1005Metric,~,,,,C144033,AF0402FR-07150KL,,,,
46,1,R416,75k,Device:R,Resistor_SMD:R_0402_1005Metric,~,,,,C137935,RC0402FR-0775KL,,,,
47,1,R420,0R,Device:R_Small,Resistor_SMD:R_0402_1005Metric,~,DNP,,,C17168,0402WGF0000TCE,,,,
48,1,R422,33k 1%,Device:R,Resistor_SMD:R_0402_1005Metric,~,,,,C138003,RC0402FR-0733KL,,,,
49,1,R424,18.7k 1%,Device:R,Resistor_SMD:R_0402_1005Metric,~,,,,C850842,AT0402BRD0718K7L,,,,
50,2,"R427, R428",1k,Device:R_Small,Resistor_SMD:R_0402_1005Metric,~,,,,C11702,C11702,,,,
51,2,"RN201, RN301",100k,Device:R_Pack04_Split,Resistor_SMD:R_Array_Convex_4x0603,~,,,,C110374,YC164-FR-07100KL,,,,
52,1,U201,T113-S3,F133:F133,CPU_Allwinner_T113-S3:LQFP-128_L14.0-W14.0-P0.40-LS16.0-BL-EP5.6,https://linux-sunxi.org/images/7/73/T113-s3_datasheet_v1.6.pdf,,,,C5197687,T113-S3,https://bbs.aw-ol.com/assets/uploads/files/1648883311855-t11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,,,
53,1,U202,W25Q32JVSS,:W25Q32JVSS_1,Package_SO:SOIC-8_5.23x5.23mm_P1.27mm,http://www.winbond.com/resource-files/w25q32jv%20revg%200327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,,,,C179173,W25Q32JVSSIQ,,,,
54,1,U203,ATECC608A-MAHDA,Security:ATECC608A-MAHDA,Package_DFN_QFN:DFN-8-1EP_3x2mm_P0.5mm_EP1.3x1.5mm,http://ww1.microchip.com/downloads/en/DeviceDoc/ATECC608A-Cr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,,,,C616908,ATECC608A-MAHDA-S,,,,
55,1,U301,ESP32-WROOM-32U,RF_Module:ESP32-WROOM-32U,RF_Module:ESP32-WROOM-32U,https://www.espressif.com/sites/default/files/documentation/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,,,,C328062,ESP32-WROOM-32U-N4,,,,
56,2,"U402, U403",SY8088IAAC,LCSC_Regulator:SY8088IAAC,Package_TO_SOT_SMD:SOT-23-5,https://item.szlcsc.com/236104.html,,,,C479072,SY8088IAAC,,,,
57,1,U404,SCT2650STER,LCSC_Regulator:SCT2650STER,Package_SO:HSOP-8-1EP_3.9x4.9mm_P1.27mm_EP2.41x3.1mm,https://datasheet.lcsc.com/lcsc/2202132000_SCT-SCT2650STER_C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,,,,C2840771,SCT2650STER,,,,
58,1,U405,SN65HVD230,Interface_CAN_LIN:SN65HVD230,Package_SO:SOIC-8_3.9x4.9mm_P1.27mm,https://datasheet.lcsc.com/lcsc/2304140030_Texas-Instruments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,,,,C12084,SN65HVD230DR,,,,
59,1,Y201,24Mhz,Device:Crystal_GND24,Crystal:Crystal_SMD_3225-4Pin_3.2x2.5mm,~,,,,C2149059,3TJ424000XYFBC,,,,

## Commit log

2024-02-15 Initial commit, submitted for fab
2024-03-14 submit for production at jlc
2024-03-23 Submit for fab rev 2
2024-06-18 Submit for production
2024-08-10 Remove unused support directory
2024-08-10 Doc updates
